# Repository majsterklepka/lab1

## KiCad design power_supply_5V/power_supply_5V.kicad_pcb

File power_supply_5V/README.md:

# Power supply module
electronics workshop

Hi! Here we have a module of standard (constant)voltage output +5V. Module is build with popular chip 7805 and a few discrete component. I have designed a PCB for it. At the same ideas, I will be create projects for various output voltage like +12V, +15V, -5V, -12V and symmetric (15 +15 Volts ...), etc. Below I publish a PCB layout 3D view

Project was made with use of [KiCad](http://http://kicad-pcb.org/ "KiCad an Open Source EDA Software") an Open Source EDA Software. Here we have a schematic sheet of the circuit:

And as for previous projects, I made PCB layout project:

## A few words of concepts

At everyday jobs, we use various things, making jobs in electronics, we use a lots of stuff, like powers supplies..., etc., so powered circuit needs supplies of powers in various, different parameters. Popular series linear IC, like 78\*\* make these jobs easily and faster to do ... Fabricated power supplies cost much more and have specialized IC inside, very often, that equipment is damaged and repair is too expensive to do, making such devices in your laboratory is simply cheaper and more economical and, in addition, raises and consolidates qualifications.

PCB is single side, easy to make in own workshop. Not all projects are that created, please remember this for the future! At my site too!

Be have a fun with that project and be happy!

_MSc. Paweł Sobótka (SQ7EQE)_

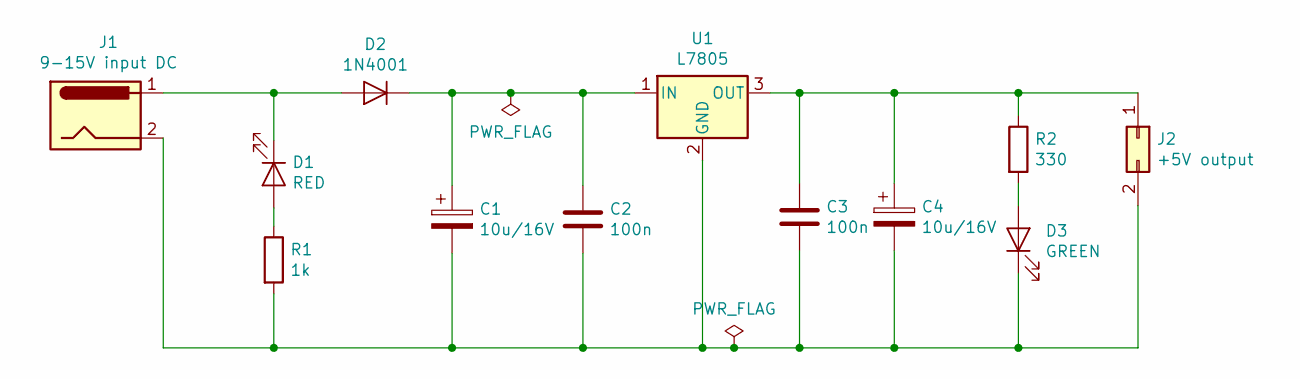
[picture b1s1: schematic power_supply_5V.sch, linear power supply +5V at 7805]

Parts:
C1, C4: 10u/16V; CP_Radial_D5.0mm_P2.50mm
C2, C3: 100n; C_Disc_D5.0mm_W2.5mm_P5.00mm
D1: RED; LED_D3.0mm
D2: 1N4001; D_DO-41_SOD81_P10.16mm_Horizontal
D3: GREEN; LED_D3.0mm
J1: 9-15V input DC; BarrelJack_CUI_PJ-063AH_Horizontal
J2: +5V output; PinConn_2x01_P2.54mm_Vertical
R1: 1k; R_Axial_DIN0207_L6.3mm_D2.5mm_P7.62mm_Horizontal
R2: 330; R_Axial_DIN0207_L6.3mm_D2.5mm_P7.62mm_Horizontal
U1: L7805; TO-220-3_Vertical

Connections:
unnamed: C1.1, C2.1, D2.1 (K), U1.1 (IN)
unnamed: C1.2, C2.2, C3.2, C4.2, D3.1 (K), J1.2, J2.2, R1.2, U1.2 (GND)
unnamed: C3.1, C4.1, J2.1, R2.1, U1.3 (OUT)
unnamed: D1.1 (K), D2.2 (A), J1.1
unnamed: D1.2 (A), R1.1
unnamed: D3.2 (A), R2.2

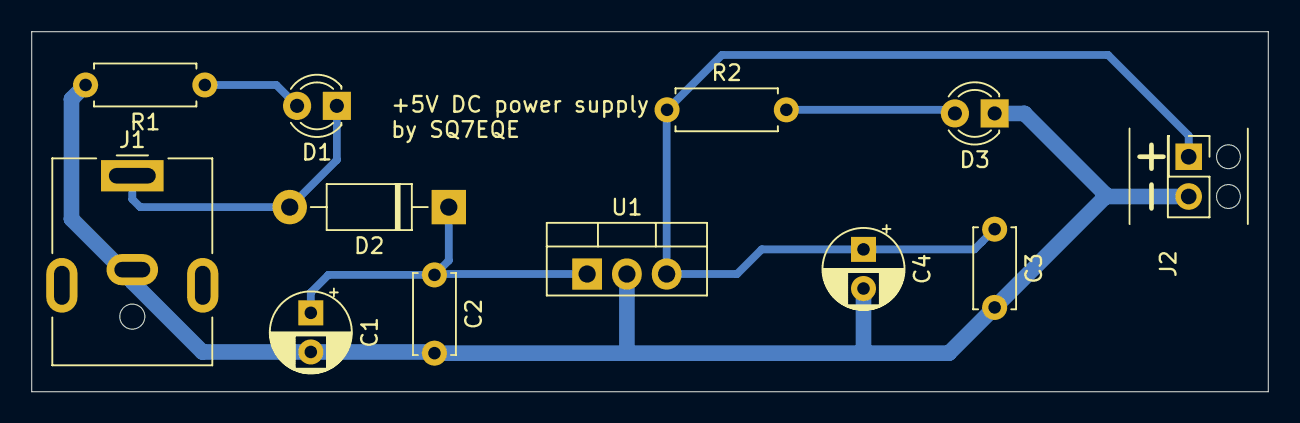
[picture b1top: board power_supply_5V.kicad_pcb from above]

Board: 2 copper layers, 79.0 x 23.0 mm, 12 parts (0 on the bottom side), 6 nets.

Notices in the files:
power_supply_5V/power_supply_5V.kicad_pcb:
GNU GPLv3
